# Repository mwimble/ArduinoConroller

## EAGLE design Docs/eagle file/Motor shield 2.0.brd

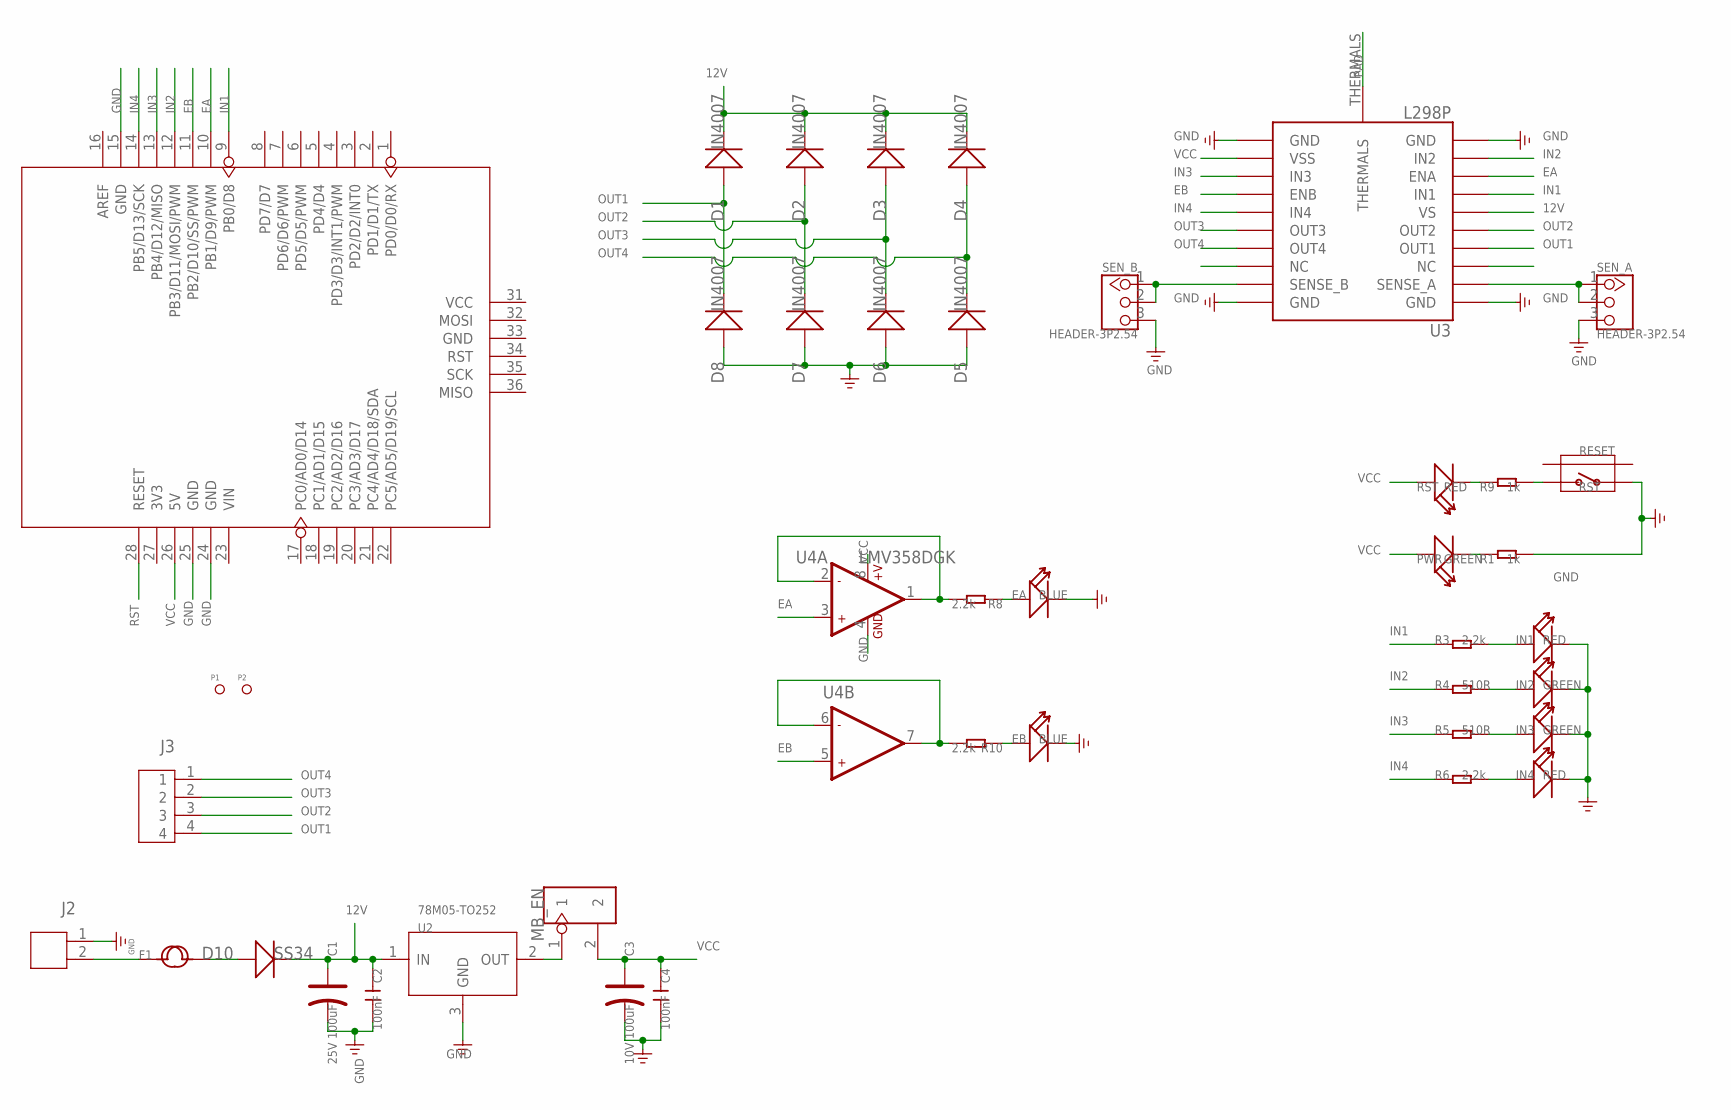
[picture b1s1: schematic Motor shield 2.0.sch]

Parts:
C1: 25V 100uF; ELECTRO-SMD-D-5.6MM
C2, C4: 100nF; C0603
C3: 10V 100uF; AVX-B
D1, D2, D3, D4, D5, D6, D7, D8: IN4007; D2010
D10: SS34; DO-214AB
EA: BLUE; D0603
EB: BLUE; D0603
F1: FUSE'RLD30P250UF'; 0311
IN1, IN4: RED; D0603
IN2, IN3: GREEN; D0603
J2: JST-2P-LEADED'3.36'; 2P-3.36-LEADED-7X7
J3: JST-4P-3.36-LEADED; 4P-3.36-LEADED-7X14
MB_EN: HEADER-2P-65/35MIL; 2P-2.54-65/35MIL
P1, P2: PAD-MARK; ROUND-MARK-1.0
PWR: GREEN; D0603
R1, R9: 1k; R0603
R3, R6, R8, R10: 2.2k; R0603
R4, R5: 510R; R0603
RESET: BUTTON-4P-REINFORCE'TS-118E'; 4P-SMD-7X3.5X3.5H
RST: RED; D0603
SEN_A: HEADER-3P2.54; 2.54_1X3P
SEN_B: HEADER-3P2.54; 2.54_1X3P
U1: ARDUINO'W/-SILK; ARDUINO
U2: 78M05-TO252; TO252
U3: L298P; POWERSO-20
U4: LMV358DGK; MSOP8

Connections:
12V: C1.+, C2.1, D1.-, D2.-, D3.-, D4.-, D10.2 (-), U2.1 (IN), U3.P$6 (VS)
EA: U1.10 (PB1/D9/PWM), U3.P$8 (ENA), U4.3 (+IN1)
EB: U1.11 (PB2/D10/SS/PWM), U3.P$14 (ENB), U4.5 (+IN2)
GND: C1.-, C2.2, C3.-, C4.2, D5.+, D6.+, D7.+, D8.+, EA.-, EB.-, IN1.-, IN2.-, IN3.-, IN4.-, J2.1, R1.2, RESET.1, SEN_A.3, SEN_B.3, U1.15 (GND), U1.24 (GND), U1.25 (GND), U2.3 (GND), U3.P$1 (GND), U3.P$10 (GND), U3.P$11 (GND), U3.P$20 (GND), U4.4 (GND)
IN1: R3.1, U1.9 (PB0/D8), U3.P$7 (IN1)
IN2: R4.1, U1.12 (PB3/D11/MOSI/PWM), U3.P$9 (IN2)
IN3: R5.1, U1.13 (PB4/D12/MISO), U3.P$13 (IN3)
IN4: R6.1, U1.14 (PB5/D13/SCK), U3.P$15 (IN4)
unnamed: IN3.+, R5.2
unnamed: MB_EN.1, U2.2 (OUT)
unnamed: PWR.-, R1.1
unnamed: SEN_A.1, SEN_A.2, U3.P$2 (SENSE_A)
unnamed: F1.1, J2.2
unnamed: D10.1 (+), F1.2
unnamed: R9.1, RST.-
unnamed: EA.+, R8.1
unnamed: IN1.+, R3.2
unnamed: IN2.+, R4.2
unnamed: EB.+, R10.1
unnamed: IN4.+, R6.2
unnamed: R10.2, U4.6 (-IN2), U4.7 (OUT2)
unnamed: R8.2, U4.1 (OUT1), U4.2 (-IN1)
unnamed: SEN_B.1, SEN_B.2, U3.P$19 (SENSE_B)
OUT1: D1.+, D8.-, J3.4, U3.P$4 (OUT1)
OUT2: D2.+, D7.-, J3.3, U3.P$5 (OUT2)
OUT3: D3.+, D6.-, J3.2, U3.P$16 (OUT3)
OUT4: D4.+, D5.-, J3.1, U3.P$17 (OUT4)
PAD: U3.THERMALS
RST: R9.2, RESET.2, U1.28 (RESET)
VCC: C3.+, C4.1, MB_EN.2, PWR.+, RST.+, U1.26 (5V), U3.P$12 (VSS), U4.8 (+V)

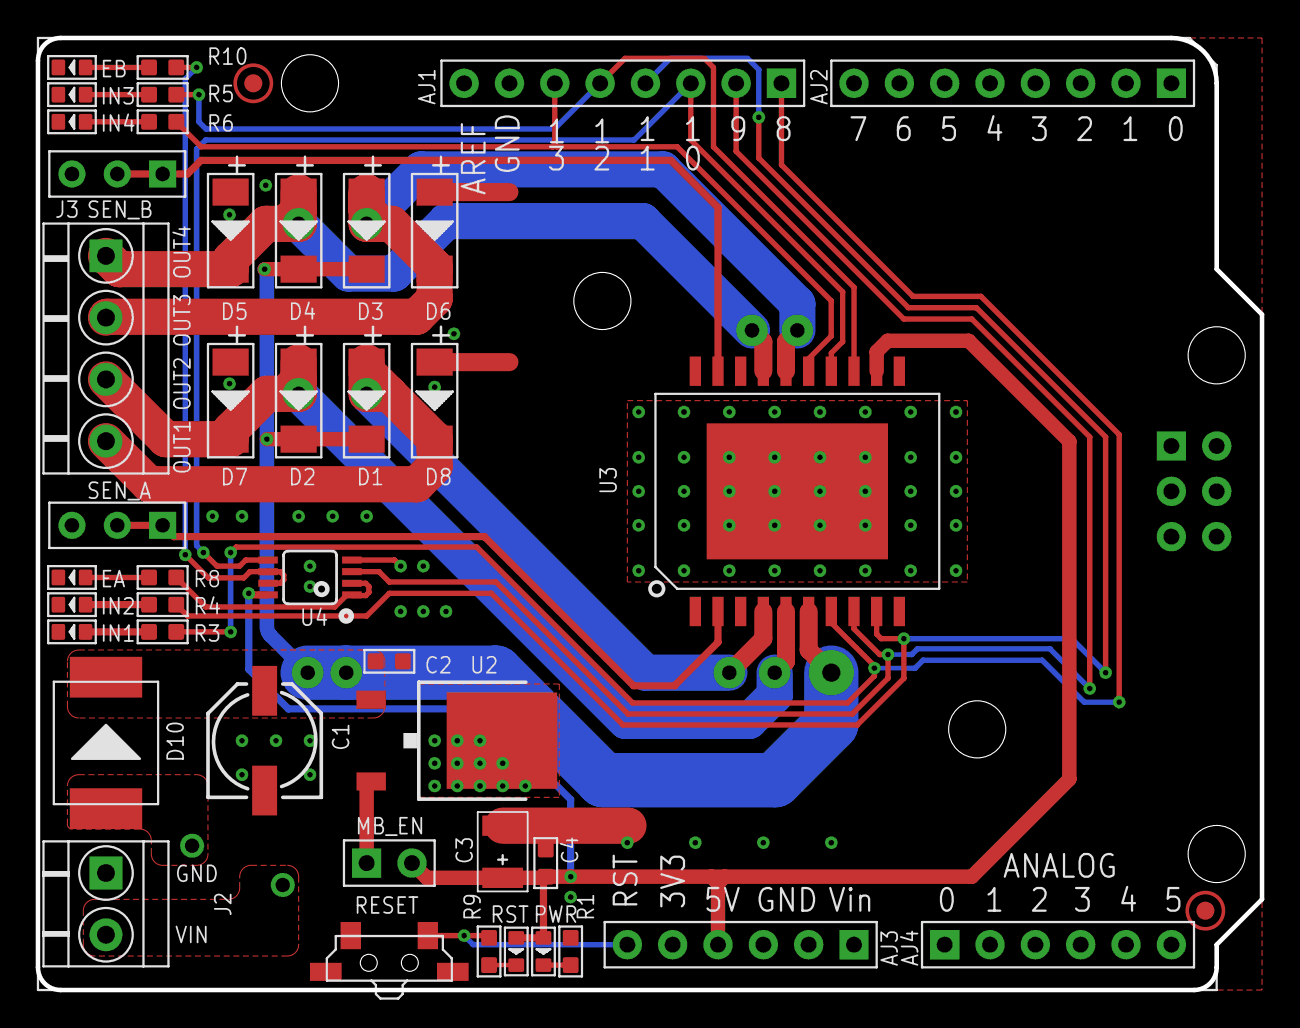
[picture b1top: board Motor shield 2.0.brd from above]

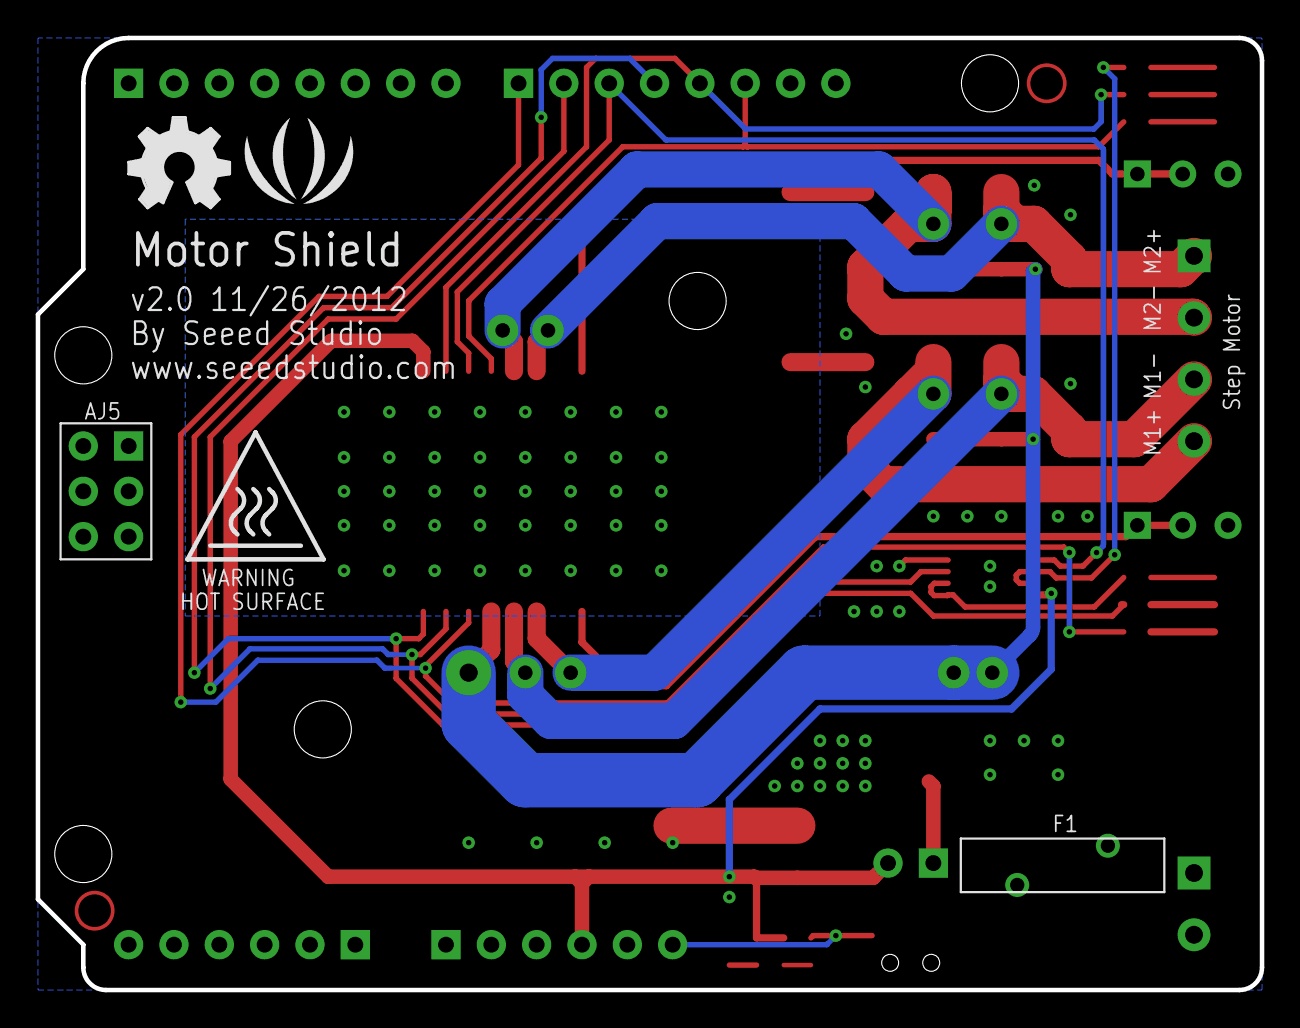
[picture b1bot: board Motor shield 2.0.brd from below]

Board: 2 copper layers, 68.6 x 53.3 mm, 44 parts (3 on the bottom side), 29 nets.

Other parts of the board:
U$15: LOGO_SILK
U$16: OSHW_FILLX200_NOTEXT

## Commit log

2015-05-04 Changes for new ISR vector name and serial communication API.
2015-05-14 5/14 snapshot on Octo
2015-05-14 Adding missing files
2015-05-15 Add new motor test and missing Arduino test sketches
2015-05-16 1200 pulses per revolution, Quadrature Encoder demo.
2015-05-18 First success at reading sensors.
2015-05-19 Added encoder.
2015-05-19 Odometer, IR sensors working on 10ms thread.
2015-05-26 Snapshot, especially i2c
2015-05-26 Somehow these were missed.
2015-05-27 Begin of adding I2CThread.h.
2015-05-30 Line finder sample code.
2015-05-30 Added ros and I2C1 tests
2015-05-30 Adding ros, boost, StandardCplusplus
2015-05-31 Adding boost / StandardCplusplus
2015-05-31 Adding libraries
2015-05-31 Trying to get Motor.h to compile
2015-05-31 Adding test ArleneArduino
2015-06-01 Honing in on ArleneArduino
2015-06-01 First attempt at threaded message receiver with queue.
2015-06-02 teleop works, too much logging, backward is only left motor.
2015-06-20 Mostly addint new Donna code -- ArduinoController/ControllerWithTimer
2015-06-20 Fixed PID to reverse correction. Logging changes.
2015-06-20 New docs, added fast motor stop, change PID correction for +/- 10 to 20.
2015-06-20 Add call to motor.FORWARD at end of FOLLOW_LINE strategy. FIND_LINE_END strategy to stop when odo exceeds 700 instead of 200.
2015-06-20 Fixes
2015-06-20 Stop logging when strategy in STOP state. Strategy FOUND_END transitions to STOP. Strategy uses static data members.
2015-06-20 Motor default speed is 64. Fix position of Motor::Forward call in strategy.
2015-06-21 Added Strategy::Dump. Made Strategy::Process static. PID now stops and turns to center line.
2015-06-21 snapshot
2015-06-22 ControllerWithTimer.ino Remove threading code. Add DEBUG flag to just show sensor data. Remove motor command queuing test code. Add code to compute statistics, such as average time to read sensors, t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
    LineSensor.h
    Change max timeout usec to 800 (from 2500) for faster sensor read.
    Remove logging.
    Make methods static.
    Strategy.h
    Enhance Dump logging with timing.
2015-06-23 ControllerWithTimer.ino * Remove threading includes
    Strategy.h
    * Add strategy to sample the left/right endpoing sensors while walking over a line, and the center sensor(s) while trying to stop after detecting the other side of the line.
2015-06-23 Added documentation and code SHA reference
2015-06-23 ControllerWithTimer.ino * Remove IMU reference. * Add Map::DumpTree() of root map node.
    IMU.h -- deleted
    LineSensor.h
    * Change calibrations to match floor model.
    Map.h -- new
    SensorStick.h
    * Made Heading a static function.
2015-06-23 Updated docs for latest code experiments
2015-06-24 ControllerWithTimer.ino * Stop strategy when the state is either STOP or SOLVED.
    Strategy.h
    * New DEAD_END_MIN_YAW and SOLVED states.
    * Add code to detect dead end lines and the stop symbol.
    * ImageLine() only samples the center line after the trailing edge as been detected and a short distance after that.
    * Small correction for number of samples required for left/continuation/right line detection.
    * When a dead end is found, go to the DEAD_END_MIN_YAW state to begin the 180 degree turn.
2015-06-24 Updated documentation after first successful maze solution.
2015-06-25 ControllerWithTimer.ino * After giving go-ahead input, delay 10 secs. Allows disconnecting the teather.
    Stragegy.h
    * Gave up using yaw for turns -- I turn until the line disappears and then keep turning until the line appears again.
    * Refactored some case switch code into separate methods.
    * Improved logging detail and made some logging enabled by constants.
    * Removed stops during turns.
    LineSensor.h
2015-06-26 Created Log class which sends logs to both Print and Print3 -- which is the XBEE radio.
2015-06-26 Updated documentation
2015-07-04 Line detection detects boxes. Begin of EwynCamera.
2015-07-04 Thresholding functionality works.
2015-07-04 New EwynCamera class with line detection for vertical lines and image annotation.
2015-07-05 Video working again. Yellow/orange lines annotated in image.
2016-02-01 Catch everything up. Kaimi in particular
2016-02-11 Basic motor functions work for Kaimi
